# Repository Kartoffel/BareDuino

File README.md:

BareDuino
===============
This repository contains the design (and other relevant) files for all the released BareDuino's.
Please visit this website for more information ----> http://www.niekproductions.com/

## License ##
All of the files in this repository are released under the BSD license.
Copyright (c) NiekProductions, 2013 All rights reserved.

Redistribution and use in source and binary forms, with or without modification, are permitted provided that the following conditions are met:
Redistributions of source code must retain the above copyright notice, this list of conditions and the following disclaimer. Redistributions in binary form must reproduce the above copyright notice, this list of conditions and the following disclaimer in the documentation and/or other materials provided with the distribution. THIS SOFTWARE IS PROVIDED BY THE COPYRIGHT HOLDERS AND CONTRIBUTORS "AS IS" AND ANY EXPRESS OR IMPLIED WARRANTIES, INCLUDING, BUT NOT LIMITED TO, THE IMPLIED WARRANTIES OF MERCHANTABILITY AND FITNESS FOR A PARTICULAR PURPOSE ARE DISCLAIMED. IN NO EVENT SHALL THE COPYRIGHT HOLDER OR CONTRIBUTORS BE LIABLE FOR ANY DIRECT, INDIRECT, INCIDENTAL, SPECIAL, EXEMPLARY, OR CONSEQUENTIAL DAMAGES (INCLUDING, BUT NOT LIMITED TO, PROCUREMENT OF SUBSTITUTE GOODS OR SERVICES; LOSS OF USE, DATA, OR PROFITS; OR BUSINESS INTERRUPTION) HOWEVER CAUSED AND ON ANY THEORY OF LIABILITY, WHETHER IN CONTRACT, STRICT LIABILITY, OR TORT (INCLUDING NEGLIGENCE OR OTHERWISE) ARISING IN ANY WAY OUT OF THE USE OF THIS SOFTWARE, EVEN IF ADVISED OF THE POSSIBILITY OF SUCH DAMAGE.

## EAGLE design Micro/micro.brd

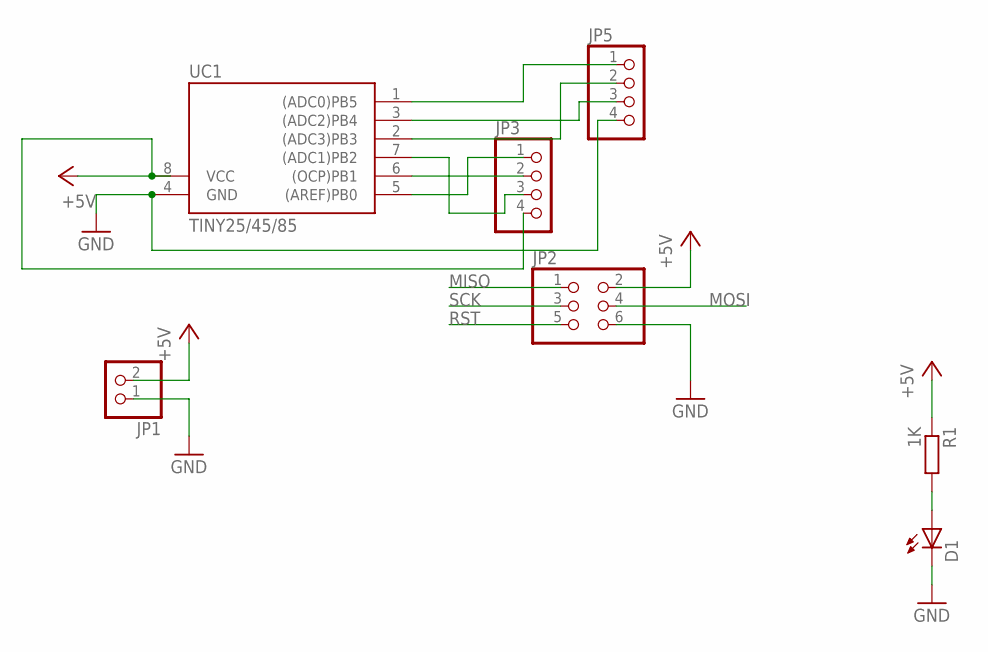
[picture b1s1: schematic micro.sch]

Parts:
D1: LED3MM
JP1: PINHD-1X02_2.54; 1X02
JP2: PINHD-2X03_2.54; 2X03
JP3, JP5: PINHD-1X4; 1X04
R1: 1K; 0207/2V
UC1: TINY25/45/85; SOIC8

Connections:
+5V: JP1.2, JP2.2, JP3.4, R1.1, UC1.8 (VCC)
GND: D1.K (C), JP1.1, JP2.6, JP5.4, UC1.4 (GND)
MISO: JP2.1, JP3.2, UC1.6 ((OCP)PB1)
MOSI: JP2.4, JP3.1, UC1.5 ((AREF)PB0)
unnamed: JP5.2, UC1.2 ((ADC3)PB3)
unnamed: JP5.3, UC1.3 ((ADC2)PB4)
unnamed: D1.A, R1.2
RST: JP2.5, JP5.1, UC1.1 ((ADC0)PB5)
SCK: JP2.3, JP3.3, UC1.7 ((ADC1)PB2)

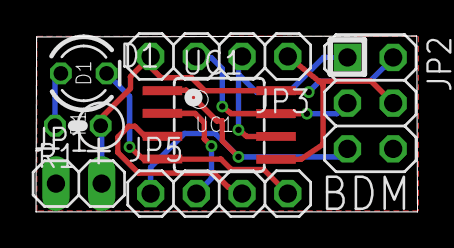
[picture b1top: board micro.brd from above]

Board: 4 copper layers, 21.2 x 9.8 mm, 7 parts (0 on the bottom side), 9 nets.

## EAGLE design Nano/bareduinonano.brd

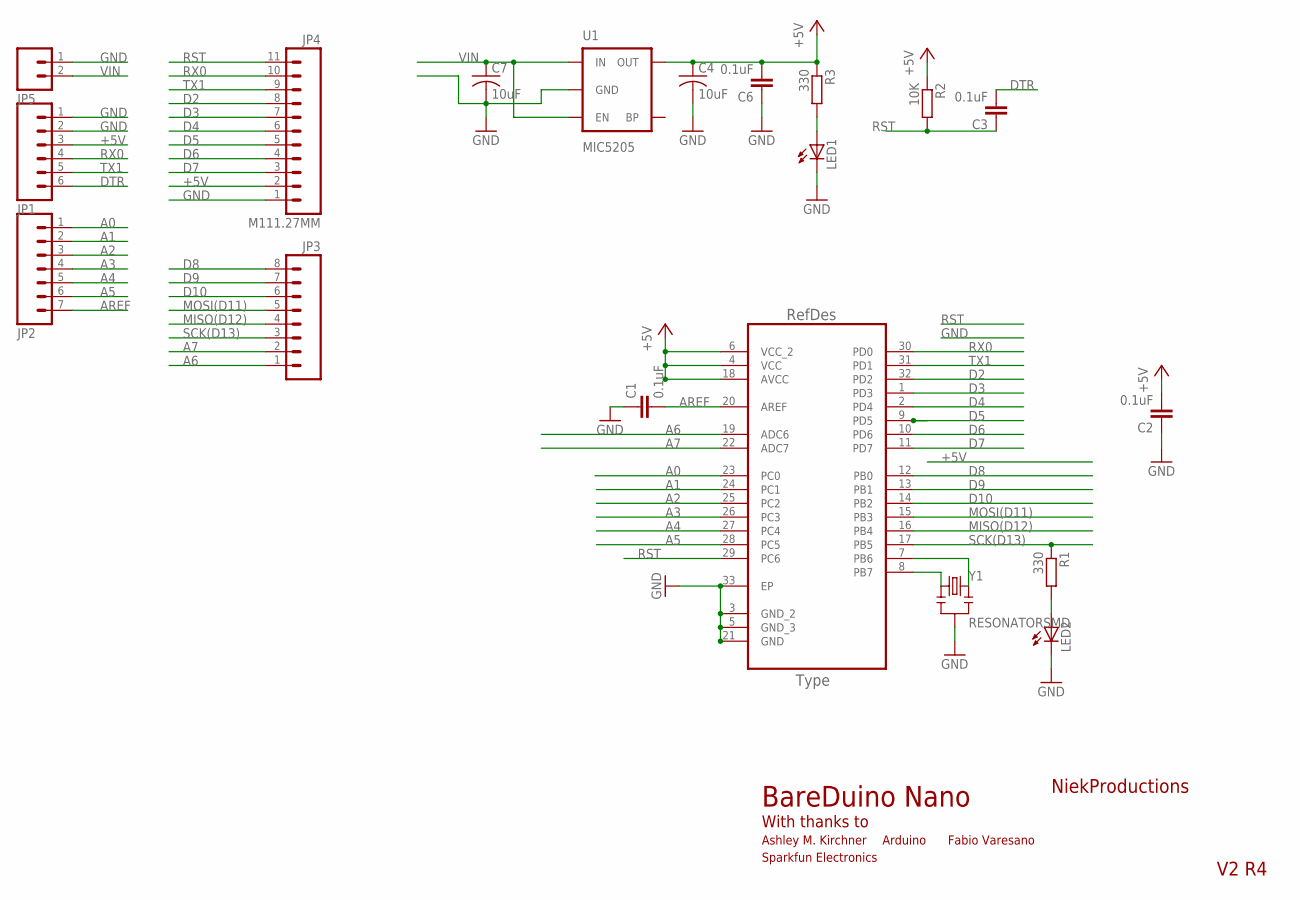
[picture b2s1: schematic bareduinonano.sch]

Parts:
C1, C2, C3, C6: 0.1uF; C0402K
C4, C7: 10uF; C0603K
JP1: M061.27MM; 1X06-1.27MM
JP2: M071.27MM; 1X07-1.27MM
JP3: M081.27MM; 1X08-1.27MM
JP4: M111.27MM; 1X11-1.27MM
JP5: M021.27MM; 1X02-1.27MM
LED1, LED2: LED0603; LED-0603
R1, R3: 330; R0402
R2: 10K; R0402
U1: MIC5205; SOT23-5
UC1: ATMEGA328P-MU; QFN50P500X500X100-33N
Y1: RESONATORSMD; RESONATOR-SMD

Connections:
+5V: C2.2, C4.1, C6.2, JP1.3, JP4.2, R2.1, R3.1, U1.5 (OUT), UC1.4 (VCC), UC1.6 (VCC_2), UC1.18 (AVCC)
A0: JP2.1, UC1.23 (PC0)
A1: JP2.2, UC1.24 (PC1)
A2: JP2.3, UC1.25 (PC2)
A3: JP2.4, UC1.26 (PC3)
A4: JP2.5, UC1.27 (PC4)
A5: JP2.6, UC1.28 (PC5)
A6: JP3.1, UC1.19 (ADC6)
A7: JP3.2, UC1.22 (ADC7)
AREF: C1.2, JP2.7, UC1.20 (AREF)
D2: JP4.8, UC1.32 (PD2)
D3: JP4.7, UC1.1 (PD3)
D4: JP4.6, UC1.2 (PD4)
D5: JP4.5, UC1.9 (PD5)
D6: JP4.4, UC1.10 (PD6)
D7: JP4.3, UC1.11 (PD7)
D8: JP3.8, UC1.12 (PB0)
D9: JP3.7, UC1.13 (PB1)
D10: JP3.6, UC1.14 (PB2)
DTR: C3.2, JP1.6
GND: C1.1, C2.1, C4.2, C6.1, C7.2, JP1.1, JP1.2, JP4.1, JP5.1, LED1.C, LED2.C, U1.2 (GND), UC1.3 (GND_2), UC1.5 (GND_3), UC1.21 (GND), UC1.33 (EP), Y1.2
MISO(D12): JP3.4, UC1.16 (PB4)
MOSI(D11): JP3.5, UC1.15 (PB3)
unnamed: UC1.8 (PB7), Y1.1
unnamed: LED2.A, R1.2
unnamed: UC1.7 (PB6), Y1.3
unnamed: LED1.A, R3.2
RST: C3.1, JP4.11, R2.2, UC1.29 (PC6)
RX0: JP1.4, JP4.10, UC1.30 (PD0)
SCK(D13): JP3.3, R1.1, UC1.17 (PB5)
TX1: JP1.5, JP4.9, UC1.31 (PD1)
VIN: C7.1, JP5.2, U1.1 (IN), U1.3 (EN)

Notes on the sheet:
BareDuino Nano
NiekProductions
V2 R4
With thanks to
Ashley M. Kirchner
Sparkfun Electronics
Arduino
Fabio Varesano

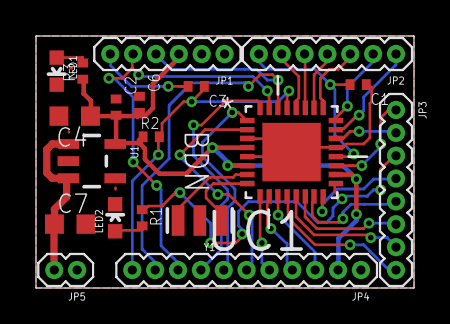
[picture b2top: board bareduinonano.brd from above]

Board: 2 copper layers, 21.0 x 14.0 mm, 19 parts (0 on the bottom side), 32 nets.

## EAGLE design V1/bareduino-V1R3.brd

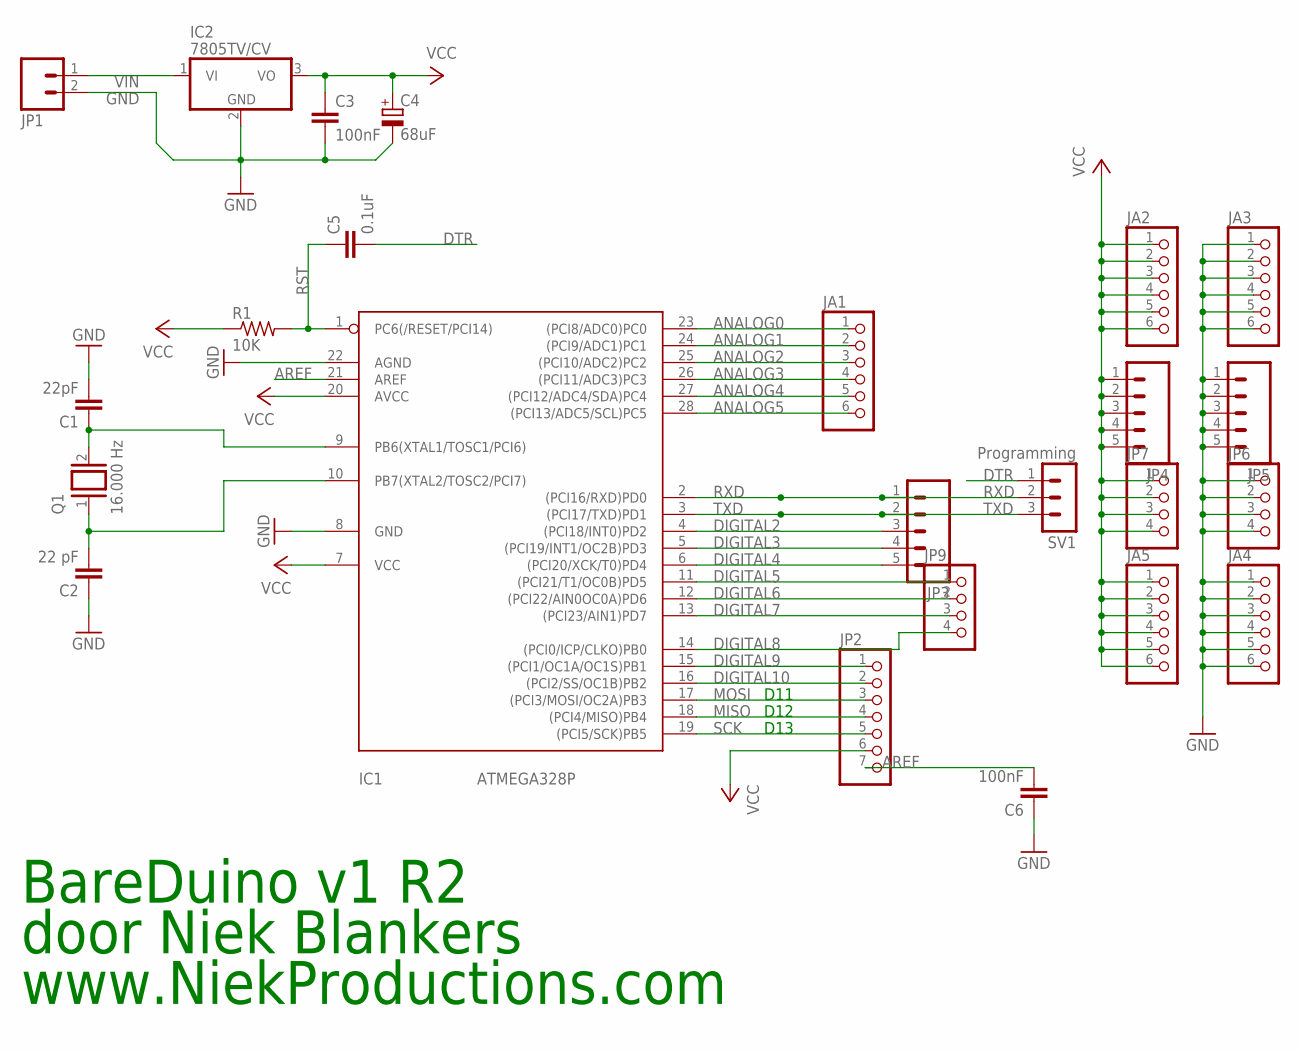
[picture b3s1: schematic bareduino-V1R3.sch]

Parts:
C1: 22pF; C025-024X044
C2: 22 pF; C025-024X044
C3: 100nF; C025-025X050
C4: 68uF; E2,5-6E
C5: 0.1uF; C025-024X044
C6: 100nF; C025-024X044
IC1: ATMEGA328P; DIL28/3
IC2: 7805TV/CV; TO220V
JA1, JA2, JA3, JA4, JA5: PINHD-1X6CB; 1X06-CLEANBIG
JP1: M025MM; SCREWTERMINAL-5MM-2
JP2: PINHD-1X07_2.54-S; 1X07-S
JP3, JP4, JP5: M05PTH; 1X05
JP6, JP7, JP9: PINHD-1X04_2.54-S; 1X04-S
Q1: 16.000 Hz; QS
R1: 10K; 0207/5V
SV1: Programming; MA03-1

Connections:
ANALOG0: IC1.23 ((PCI8/ADC0)PC0), JA1.1
ANALOG1: IC1.24 ((PCI9/ADC1)PC1), JA1.2
ANALOG2: IC1.25 ((PCI10/ADC2)PC2), JA1.3
ANALOG3: IC1.26 ((PCI11/ADC3)PC3), JA1.4
ANALOG4: IC1.27 ((PCI12/ADC4/SDA)PC4), JA1.5
ANALOG5: IC1.28 ((PCI13/ADC5/SCL)PC5), JA1.6
AREF: C6.2, IC1.21 (AREF), JP2.7
DIGITAL2: IC1.4 ((PCI18/INT0)PD2), JP3.3
DIGITAL3: IC1.5 ((PCI19/INT1/OC2B)PD3), JP3.4
DIGITAL4: IC1.6 ((PCI20/XCK/T0)PD4), JP3.5
DIGITAL5: IC1.11 ((PCI21/T1/OC0B)PD5), JP9.1
DIGITAL6: IC1.12 ((PCI22/AIN0OC0A)PD6), JP9.2
DIGITAL7: IC1.13 ((PCI23/AIN1)PD7), JP9.3
DIGITAL8: IC1.14 ((PCI0/ICP/CLKO)PB0), JP9.4
DIGITAL9: IC1.15 ((PCI1/OC1A/OC1S)PB1), JP2.1
DIGITAL10: IC1.16 ((PCI2/SS/OC1B)PB2), JP2.2
DTR: C5.2, SV1.1
GND: C1.2, C2.1, C3.2, C4.-, C6.1, IC1.8 (GND), IC1.22 (AGND), IC2.2 (GND), JA3.1, JA3.2, JA3.3, JA3.4, JA3.5, JA3.6, JA4.1, JA4.2, JA4.3, JA4.4, JA4.5, JA4.6, JP1.2, JP5.1, JP5.2, JP5.3, JP5.4, JP5.5, JP6.1, JP6.2, JP6.3, JP6.4
MISO: IC1.18 ((PCI4/MISO)PB4), JP2.4
MOSI: IC1.17 ((PCI3/MOSI/OC2A)PB3), JP2.3
unnamed: C2.2, IC1.10 (PB7(XTAL2/TOSC2/PCI7)), Q1.1
unnamed: C1.1, IC1.9 (PB6(XTAL1/TOSC1/PCI6)), Q1.2
RST: C5.1, IC1.1 (PC6(/RESET/PCI14)), R1.2
RXD: IC1.2 ((PCI16/RXD)PD0), JP3.1, SV1.2
SCK: IC1.19 ((PCI5/SCK)PB5), JP2.5
TXD: IC1.3 ((PCI17/TXD)PD1), JP3.2, SV1.3
VCC: C3.1, C4.+, IC1.7 (VCC), IC1.20 (AVCC), IC2.3 (VO), JA2.1, JA2.2, JA2.3, JA2.4, JA2.5, JA2.6, JA5.1, JA5.2, JA5.3, JA5.4, JA5.5, JA5.6, JP2.6, JP4.1, JP4.2, JP4.3, JP4.4, JP4.5, JP7.1, JP7.2, JP7.3, JP7.4, R1.1
VIN: IC2.1 (VI), JP1.1

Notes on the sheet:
D11
D12
D13
BareDuino v1 R2
door Niek Blankers
www.NiekProductions.com

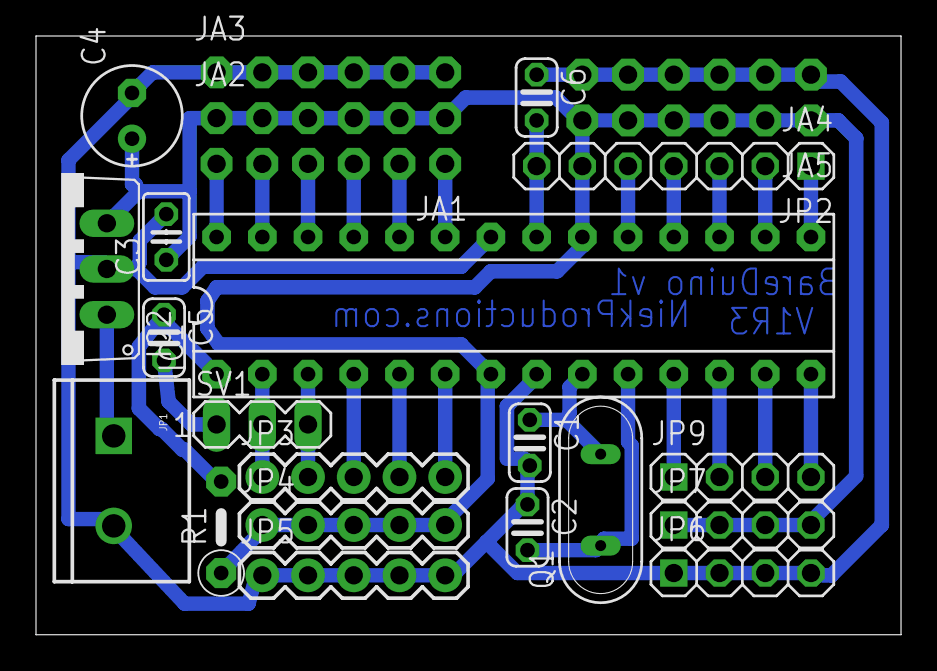
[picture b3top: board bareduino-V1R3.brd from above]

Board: 2 copper layers, 48.1 x 33.3 mm, 24 parts (0 on the bottom side), 28 nets.

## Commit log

2013-06-28 Initial commit
    Contains the original bareduino, the bareduino nano and the bareduino
    micro.
2013-08-15 Nano product pictures
2013-08-15 Redrawn BareDuino Micro
